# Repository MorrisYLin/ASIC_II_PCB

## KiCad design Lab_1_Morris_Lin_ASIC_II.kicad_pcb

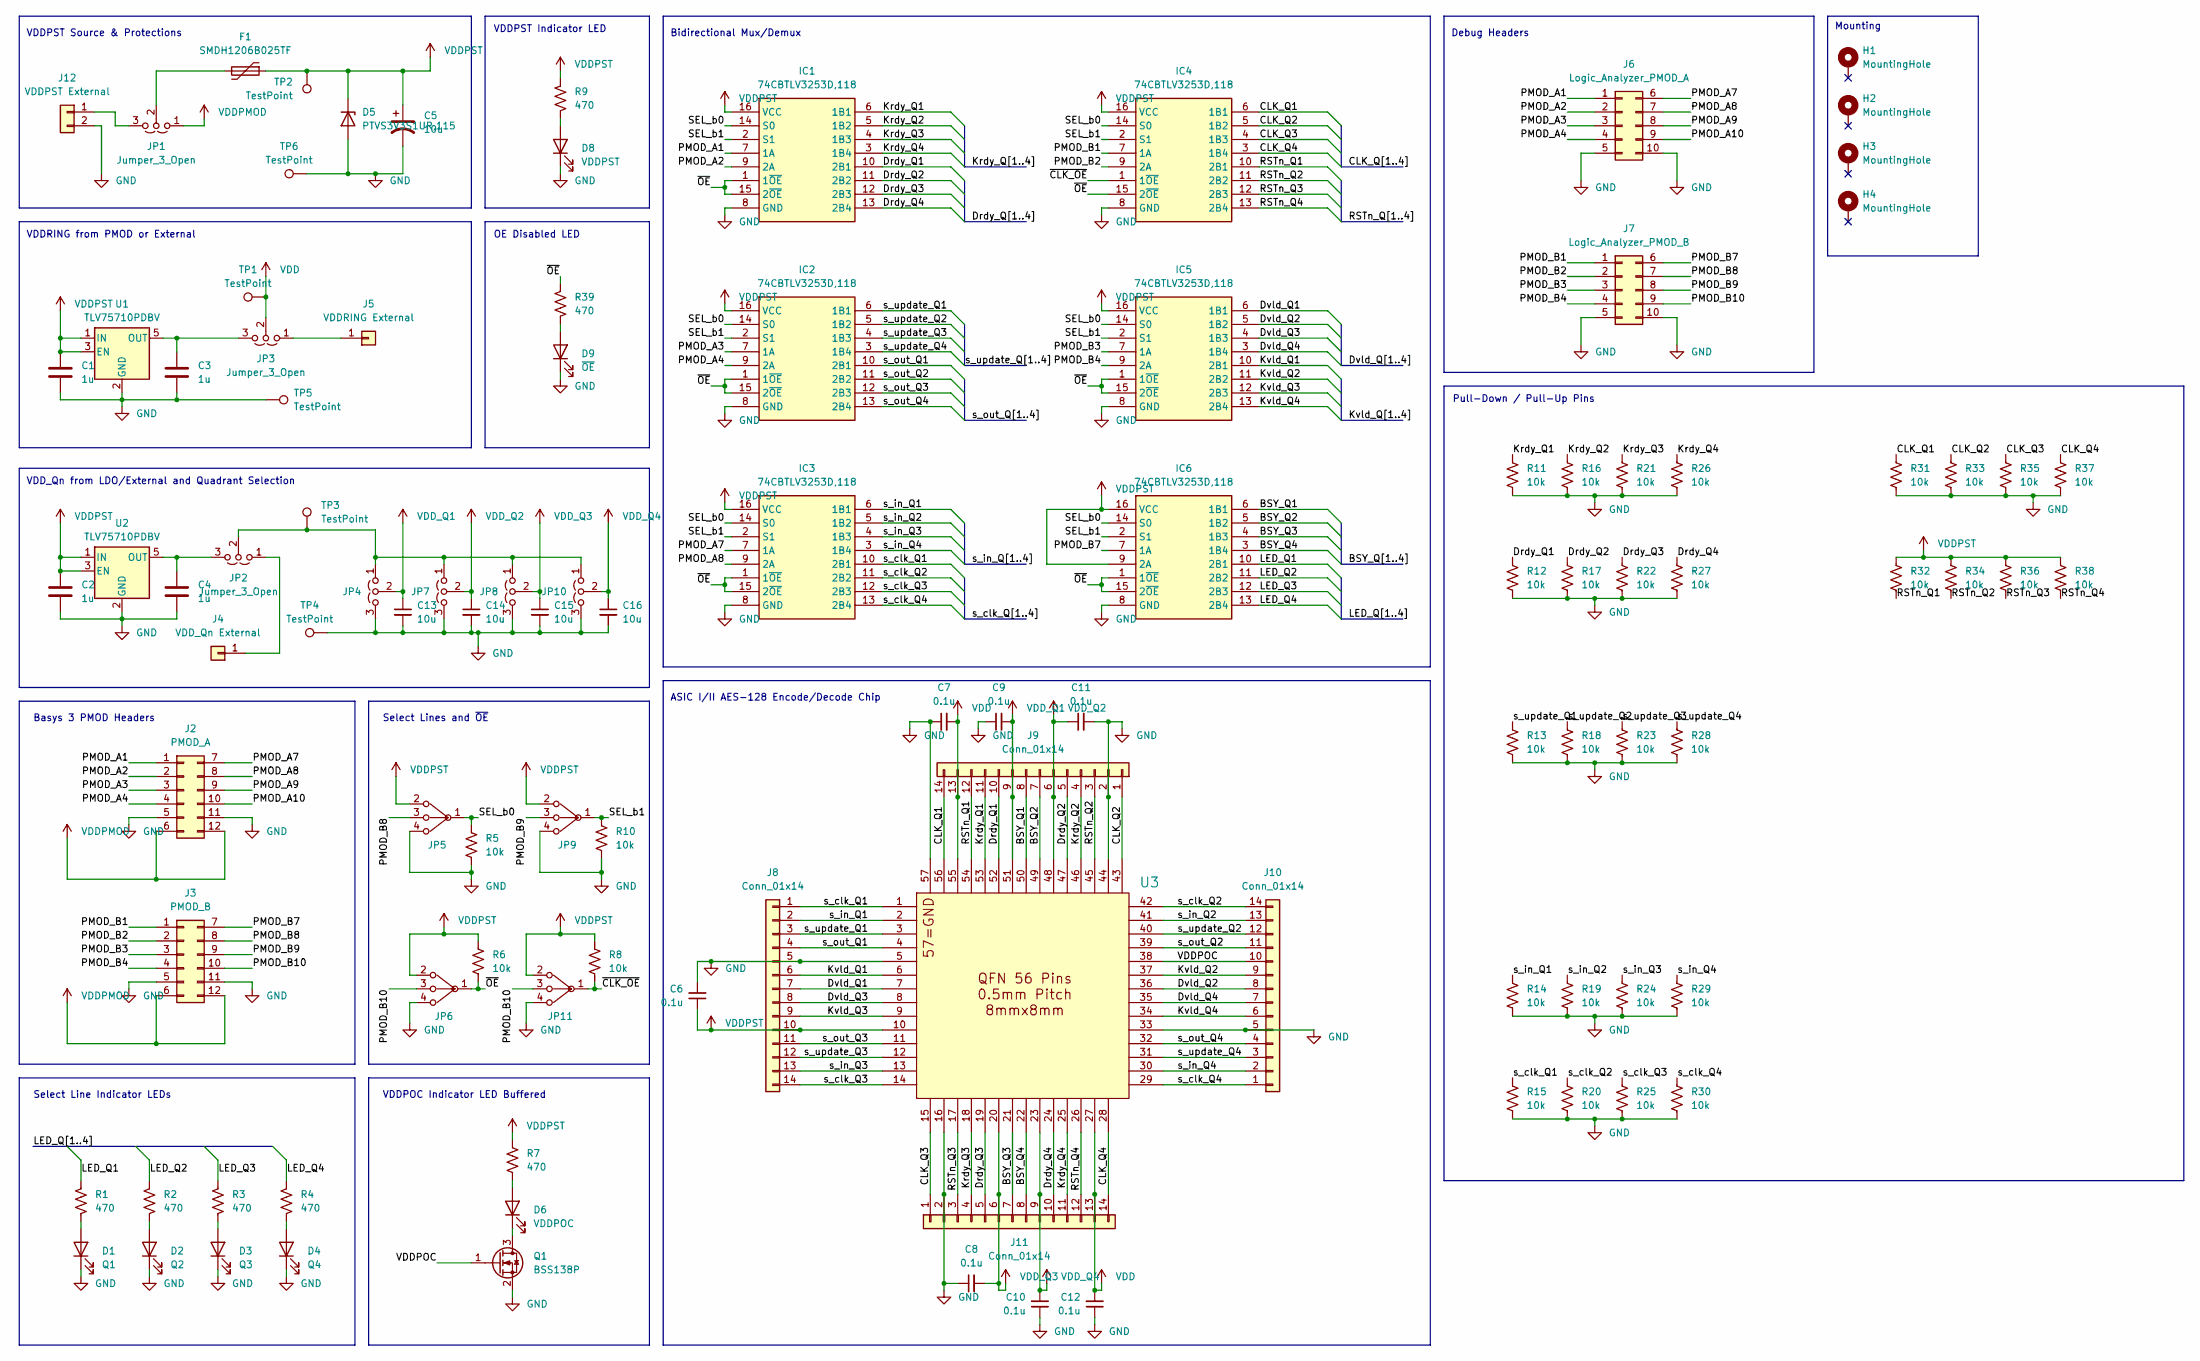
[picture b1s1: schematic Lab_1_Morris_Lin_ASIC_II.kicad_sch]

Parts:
C1, C2, C3, C4: 1u; C_1206_3216Metric_Pad1.33x1.80mm_HandSolder; Mouser Part Number 187-CL31B105KAHNFNE
C5, C13, C14, C15, C16: 10u; C_1206_3216Metric_Pad1.33x1.80mm_HandSolder; Mouser Part Number 187-CL31A106KAHNNNF
C6, C7, C8, C9, C10, C11, C12: 0.1u; C_1206_3216Metric_Pad1.33x1.80mm_HandSolder; Mouser Part Number 187-CL31B104KBCNFNC
D1: Q1; LED_1206_3216Metric_Pad1.42x1.75mm_HandSolder; Mouser Part Number 859-LTST-C230KRKT
D2: Q2; LED_1206_3216Metric_Pad1.42x1.75mm_HandSolder; Mouser Part Number 859-LTST-C230KRKT
D3: Q3; LED_1206_3216Metric_Pad1.42x1.75mm_HandSolder; Mouser Part Number 859-LTST-C230KRKT
D4: Q4; LED_1206_3216Metric_Pad1.42x1.75mm_HandSolder; Mouser Part Number 859-LTST-C230KRKT
D5: PTVS3V3S1UR,115; Nexperia_CFP3_SOD-123W; Mouser Part Number 771-PTVS3V3S1UR115
D6: VDDPOC; LED_1206_3216Metric_Pad1.42x1.75mm_HandSolder; Mouser Part Number 859-LTST-C230KRKT
D8: VDDPST; LED_1206_3216Metric_Pad1.42x1.75mm_HandSolder; Mouser Part Number 859-LTST-C230KRKT
D9: ~{OE}; LED_1206_3216Metric_Pad1.42x1.75mm_HandSolder; Mouser Part Number 859-LTST-C230KRKT
F1: SMDH1206B025TF; Fuse_1206_3216Metric_Pad1.42x1.75mm_HandSolder; Mouser Part Number 603-SMDH1206B025TF
H1, H2, H3, H4: MountingHole; MountingHole_3.2mm_M3_DIN965_Pad_TopBottom
IC1, IC2, IC3, IC4, IC5, IC6: 74CBTLV3253D,118; SOIC127P600X175-16N; Mouser Part Number 771-74CBTLV3253D118
J2: PMOD_A; PinHeader_2x06_P2.54mm_Horizontal; Mouser Part Number 649-1012938291203BLF
J3: PMOD_B; PinHeader_2x06_P2.54mm_Horizontal; Mouser Part Number 649-1012938291203BLF
J4: VDD_Qn External; Banana_Jack_1Pin
J5: VDDRING External; Banana_Jack_1Pin
J6: Logic_Analyzer_PMOD_A; PinHeader_VertNum_2x05_P2.54mm_Vertical
J7: Logic_Analyzer_PMOD_B; PinHeader_VertNum_2x05_P2.54mm_Vertical
J8, J9, J10, J11: Conn_01x14; PinHeader_1x14_P2.54mm_Vertical
J12: VDDPST External; Banana_Jack_2Pin
JP1, JP2, JP3, JP4, JP7, JP8, JP10: Jumper_3_Open; PinHeader_1x03_P2.54mm_Vertical
JP5, JP6, JP9, JP11: Jumper_3_Open; PinHeader_SP3T_P2.54mm_Vertical
Q1: BSS138P; SOT-23; Mouser Part Number 771-BSS138P215
R1, R2, R3, R4, R7, R9, R39: 470; R_1206_3216Metric_Pad1.30x1.75mm_HandSolder; Mouser Part Number 603-RC1206FR-13470RL
R5, R6, R8, R10, R11, R12, R13, R14, R15, R16, R17, R18, R19, R20, R21, R22, R23, R24, R25, R26, R27, R28, R29, R30, R31, R32, R33, R34, R35, R36, R37, R38: 10k; R_1206_3216Metric_Pad1.30x1.75mm_HandSolder; Mouser Part Number 603-RC1206JR-0710KP
TP1, TP2, TP3, TP4, TP5, TP6: TestPoint; TestPoint_Loop_D2.54mm_Drill1.5mm_Beaded
U1, U2: TLV75710PDBV; SOT-23-5; Mouser Part Number 595-TLV75710PDBVR
U3: QFN56ASIC

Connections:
/BSY_Q1: IC6.6 (1B1), J9.8, U3.50
/BSY_Q2: IC6.5 (1B2), J9.7, U3.49
/BSY_Q3: IC6.4 (1B3), J11.7, U3.21
/BSY_Q4: IC6.3 (1B4), J11.8, U3.22
/CLK_Q1: IC4.6 (1B1), J9.14, R31.1, U3.56
/CLK_Q2: IC4.5 (1B2), J9.1, R33.1, U3.43
/CLK_Q3: IC4.4 (1B3), J11.1, R35.1, U3.15
/CLK_Q4: IC4.3 (1B4), J11.14, R37.1, U3.28
/Drdy_Q1: IC1.10 (2B1), J9.10, R12.1, U3.52
/Drdy_Q2: IC1.11 (2B2), J9.5, R17.1, U3.47
/Drdy_Q3: IC1.12 (2B3), J11.5, R22.1, U3.19
/Drdy_Q4: IC1.13 (2B4), J11.10, R27.1, U3.24
/Dvld_Q1: IC5.6 (1B1), J8.7, U3.7
/Dvld_Q2: IC5.5 (1B2), J10.8, U3.36
/Dvld_Q3: IC5.4 (1B3), J8.8, U3.8
/Dvld_Q4: IC5.3 (1B4), J10.7, U3.35
/Krdy_Q1: IC1.6 (1B1), J9.11, R11.1, U3.53
/Krdy_Q2: IC1.5 (1B2), J9.4, R16.1, U3.46
/Krdy_Q3: IC1.4 (1B3), J11.4, R21.1, U3.18
/Krdy_Q4: IC1.3 (1B4), J11.11, R26.1, U3.25
/Kvld_Q1: IC5.10 (2B1), J8.6, U3.6
/Kvld_Q2: IC5.11 (2B2), J10.9, U3.37
/Kvld_Q3: IC5.12 (2B3), J8.9, U3.9
/Kvld_Q4: IC5.13 (2B4), J10.6, U3.34
/LED_Q1: IC6.10 (2B1), R1.1
/LED_Q2: IC6.11 (2B2), R2.1
/LED_Q3: IC6.12 (2B3), R3.1
/LED_Q4: IC6.13 (2B4), R4.1
/PMOD_A1: IC1.7 (1A), J2.1, J6.1
/PMOD_A2: IC1.9 (2A), J2.2, J6.2
/PMOD_A3: IC2.7 (1A), J2.3, J6.3
/PMOD_A4: IC2.9 (2A), J2.4, J6.4
/PMOD_A7: IC3.7 (1A), J2.7, J6.6
/PMOD_A8: IC3.9 (2A), J2.8, J6.7
/PMOD_A9: J2.9, J6.8
/PMOD_A10: J2.10, J6.9
/PMOD_B1: IC4.7 (1A), J3.1, J7.1
/PMOD_B2: IC4.9 (2A), J3.2, J7.2
/PMOD_B3: IC5.7 (1A), J3.3, J7.3
/PMOD_B4: IC5.9 (2A), J3.4, J7.4
/PMOD_B7: IC6.7 (1A), J3.7, J7.6
/PMOD_B8: J3.8, J7.7, JP5.3 (C)
/PMOD_B9: J3.9, J7.8, JP9.3 (C)
/PMOD_B10: J3.10, J7.9, JP6.3 (C), JP11.3 (C)
/RSTn_Q1: IC4.10 (2B1), J9.12, R32.2, U3.54
/RSTn_Q2: IC4.11 (2B2), J9.3, R34.2, U3.45
/RSTn_Q3: IC4.12 (2B3), J11.3, R36.2, U3.17
/RSTn_Q4: IC4.13 (2B4), J11.12, R38.2, U3.26
/SEL_b0: IC1.14 (S0), IC2.14 (S0), IC3.14 (S0), IC4.14 (S0), IC5.14 (S0), IC6.14 (S0), JP5.1 (A), R5.1
/SEL_b1: IC1.2 (S1), IC2.2 (S1), IC3.2 (S1), IC4.2 (S1), IC5.2 (S1), IC6.2 (S1), JP9.1 (A), R10.1
/VDDPOC: J10.10, Q1.1 (G), U3.38
/s_clk_Q1: IC3.10 (2B1), J8.1, R15.1, U3.1
/s_clk_Q2: IC3.11 (2B2), J10.14, R20.1, U3.42
/s_clk_Q3: IC3.12 (2B3), J8.14, R25.1, U3.14
/s_clk_Q4: IC3.13 (2B4), J10.1, R30.1, U3.29
/s_in_Q1: IC3.6 (1B1), J8.2, R14.1, U3.2
/s_in_Q2: IC3.5 (1B2), J10.13, R19.1, U3.41
/s_in_Q3: IC3.4 (1B3), J8.13, R24.1, U3.13
/s_in_Q4: IC3.3 (1B4), J10.2, R29.1, U3.30
/s_out_Q1: IC2.10 (2B1), J8.4, U3.4
/s_out_Q2: IC2.11 (2B2), J10.11, U3.39
/s_out_Q3: IC2.12 (2B3), J8.11, U3.11
/s_out_Q4: IC2.13 (2B4), J10.4, U3.32
/s_update_Q1: IC2.6 (1B1), J8.3, R13.1, U3.3
/s_update_Q2: IC2.5 (1B2), J10.12, R18.1, U3.40
/s_update_Q3: IC2.4 (1B3), J8.12, R23.1, U3.12
/s_update_Q4: IC2.3 (1B4), J10.3, R28.1, U3.31
/~CLK_OE: IC4.1 (1~OE), JP11.1 (A), R8.2
/~OE: IC1.1 (1~OE), IC1.15 (2~OE), IC2.1 (1~OE), IC2.15 (2~OE), IC3.1 (1~OE), IC3.15 (2~OE), IC4.15 (2~OE), IC5.1 (1~OE), IC5.15 (2~OE), IC6.1 (1~OE), IC6.15 (2~OE), JP6.1 (A), R6.2, R39.1
GND: C1.2, C2.2, C3.2, C4.2, C5.2, C6.2, C7.1, C8.1, C9.1, C10.1, C11.2, C12.1, C13.2, C14.2, C15.2, C16.2, D1.1 (K), D2.1 (K), D3.1 (K), D4.1 (K), D5.2 (A), D8.1 (K), D9.1 (K), IC1.8 (GND), IC2.8 (GND), IC3.8 (GND), IC4.8 (GND), IC5.8 (GND), IC6.8 (GND), J2.5, J2.11, J3.5, J3.11, J6.5, J6.10, J7.5, J7.10, J8.5, J9.2, J10.5, J11.2, J12.2, JP4.3 (B), JP5.4 (D), JP6.4 (D), JP7.3 (B), JP8.3 (B), JP9.4 (D), JP10.3 (B), JP11.4 (D), Q1.2 (S), R5.2, R10.2, R11.2, R12.2, R13.2, R14.2, R15.2, R16.2, R17.2, R18.2, R19.2, R20.2, R21.2, R22.2, R23.2, R24.2, R25.2, R26.2, R27.2, R28.2, R29.2, R30.2, R31.2, R33.2, R35.2, R37.2, TP4.1 (1_1), TP5.1 (1_1), TP6.1 (1_1), U1.2 (GND), U2.2 (GND), U3.5, U3.16, U3.33, U3.44, U3.57
unnamed: D1.2 (A), R1.2
unnamed: D2.2 (A), R2.2
unnamed: D3.2 (A), R3.2
unnamed: D4.2 (A), R4.2
unnamed: D6.2 (A), R7.2
unnamed: D6.1 (K), Q1.3 (D)
unnamed: D8.2 (A), R9.2
unnamed: D9.2 (A), R39.2
unnamed: J4.1 (Pin_1_1), JP2.1 (A)
unnamed: J5.1 (Pin_1_1), JP3.1 (A)
unnamed: J12.1, JP1.3 (B)
unnamed: F1.2, JP1.2 (C)
unnamed: C4.1, JP2.3 (B), U2.5 (OUT)
unnamed: C3.1, JP3.3 (B), U1.5 (OUT)
unnamed: JP2.2 (C), JP4.1 (A), JP7.1 (A), JP8.1 (A), JP10.1 (A), TP3.1 (1_1)
VDD: C7.2, C12.2, J9.13, J11.13, JP3.2 (C), TP1.1 (1_1), U3.27, U3.55
VDDPMOD: J2.6, J2.12, J3.6, J3.12, JP1.1 (A)
VDDPST: C1.1, C2.1, C5.1, C6.1, D5.1 (K), F1.1, IC1.16 (VCC), IC2.16 (VCC), IC3.16 (VCC), IC4.16 (VCC), IC5.16 (VCC), IC6.9 (2A), IC6.16 (VCC), J8.10, JP5.2 (B), JP6.2 (B), JP9.2 (B), JP11.2 (B), R6.1, R7.1, R8.1, R9.1, R32.1, R34.1, R36.1, R38.1, TP2.1 (1_1), U1.1 (IN), U1.3 (EN), U2.1 (IN), U2.3 (EN), U3.10
VDD_Q1: C9.2, C13.1, J9.9, JP4.2 (C), U3.51
VDD_Q2: C11.1, C14.1, J9.6, JP7.2 (C), U3.48
VDD_Q3: C8.2, C15.1, J11.6, JP8.2 (C), U3.20
VDD_Q4: C10.2, C16.1, J11.9, JP10.2 (C), U3.23

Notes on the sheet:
Select Lines and ~{OE}
VDDRING from PMOD or External
VDDPOC Indicator LED Buffered
VDDPST Indicator LED
Mounting
Select Line Indicator LEDs
ASIC I/II AES-128 Encode/Decode Chip
VDD_Qn from LDO/External and Quadrant Selection
OE Disabled LED
Bidirectional Mux/Demux
Basys 3 PMOD Headers
VDDPST Source & Protections
Pull-Down / Pull-Up Pins
Debug Headers

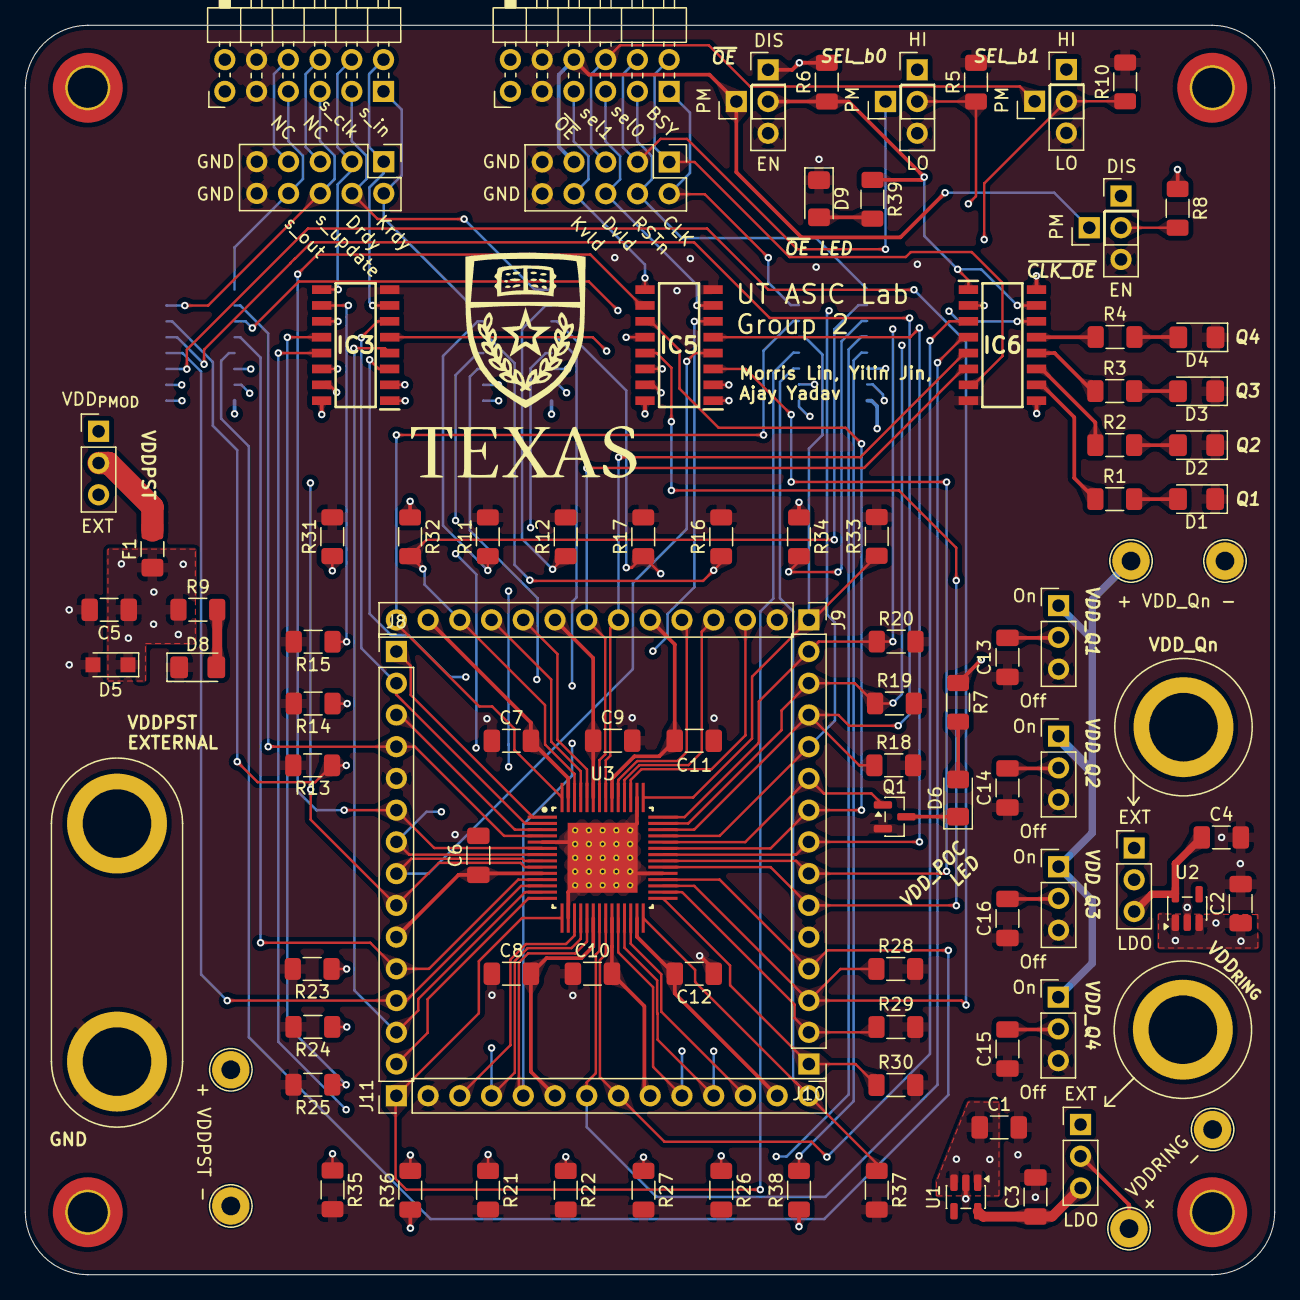
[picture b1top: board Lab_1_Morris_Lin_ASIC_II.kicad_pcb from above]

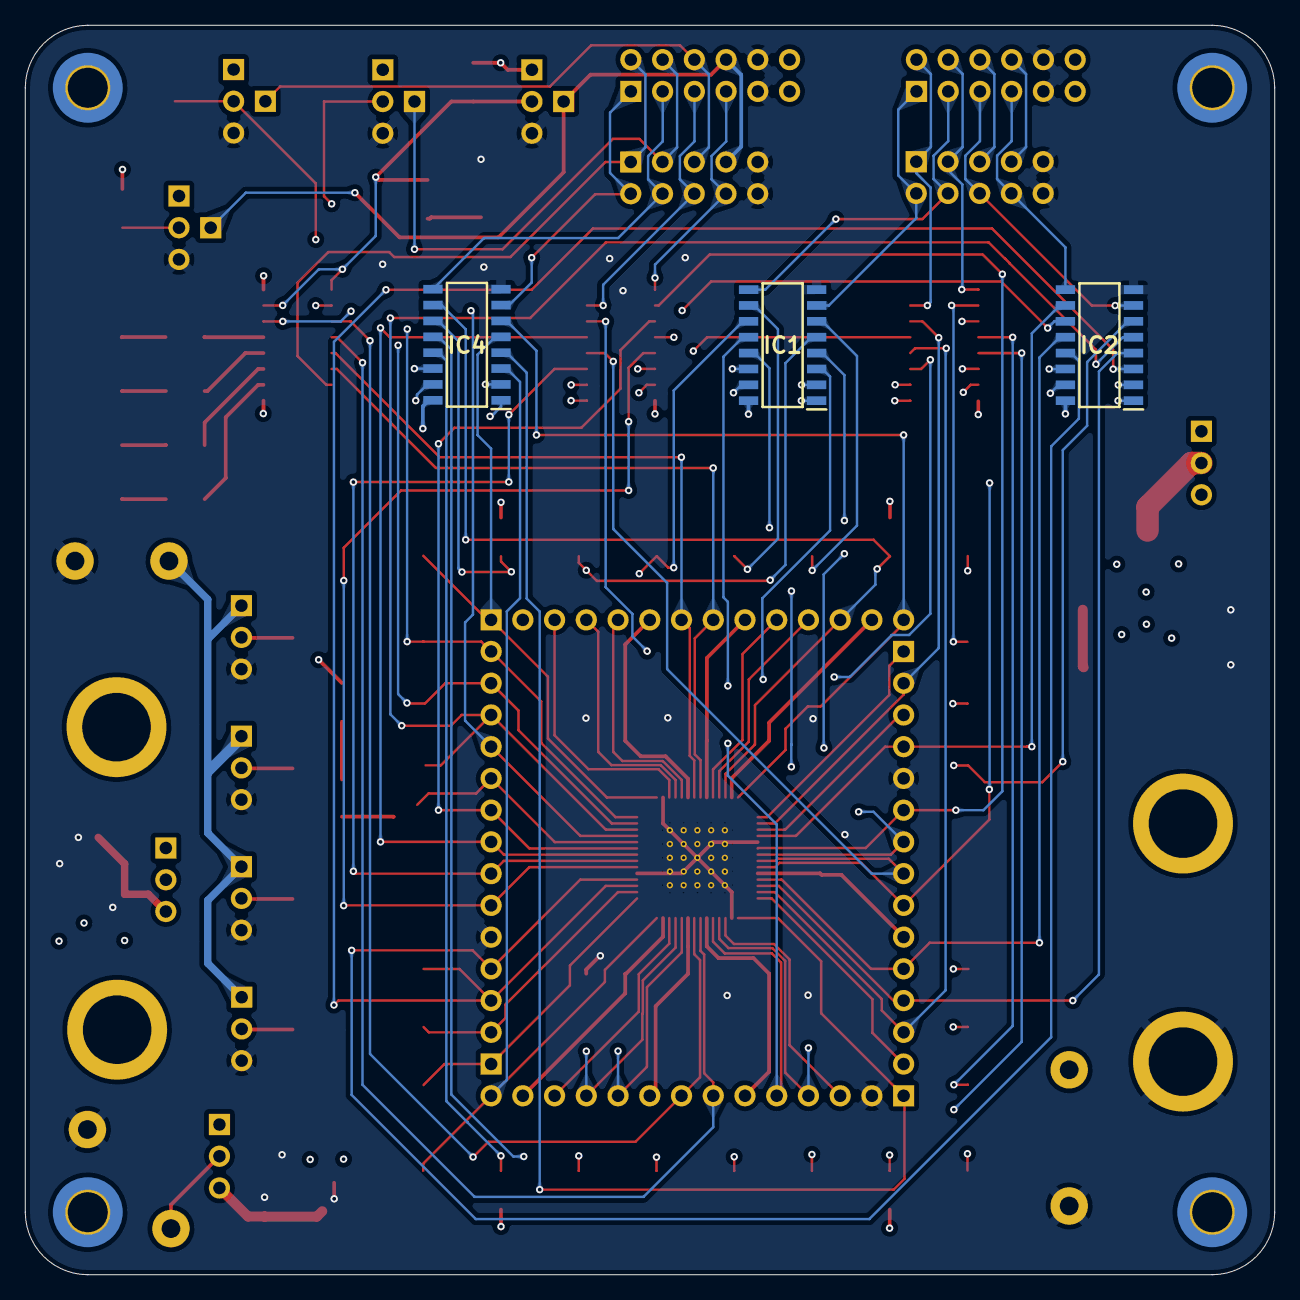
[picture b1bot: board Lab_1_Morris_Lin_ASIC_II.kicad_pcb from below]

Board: 4 copper layers, 100.0 x 100.0 mm, 106 parts (4 on the bottom side), 92 nets.
